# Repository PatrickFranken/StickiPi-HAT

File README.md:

# StickiPi-HAT
RaspberryPI HAT for the Sticki flightlogger

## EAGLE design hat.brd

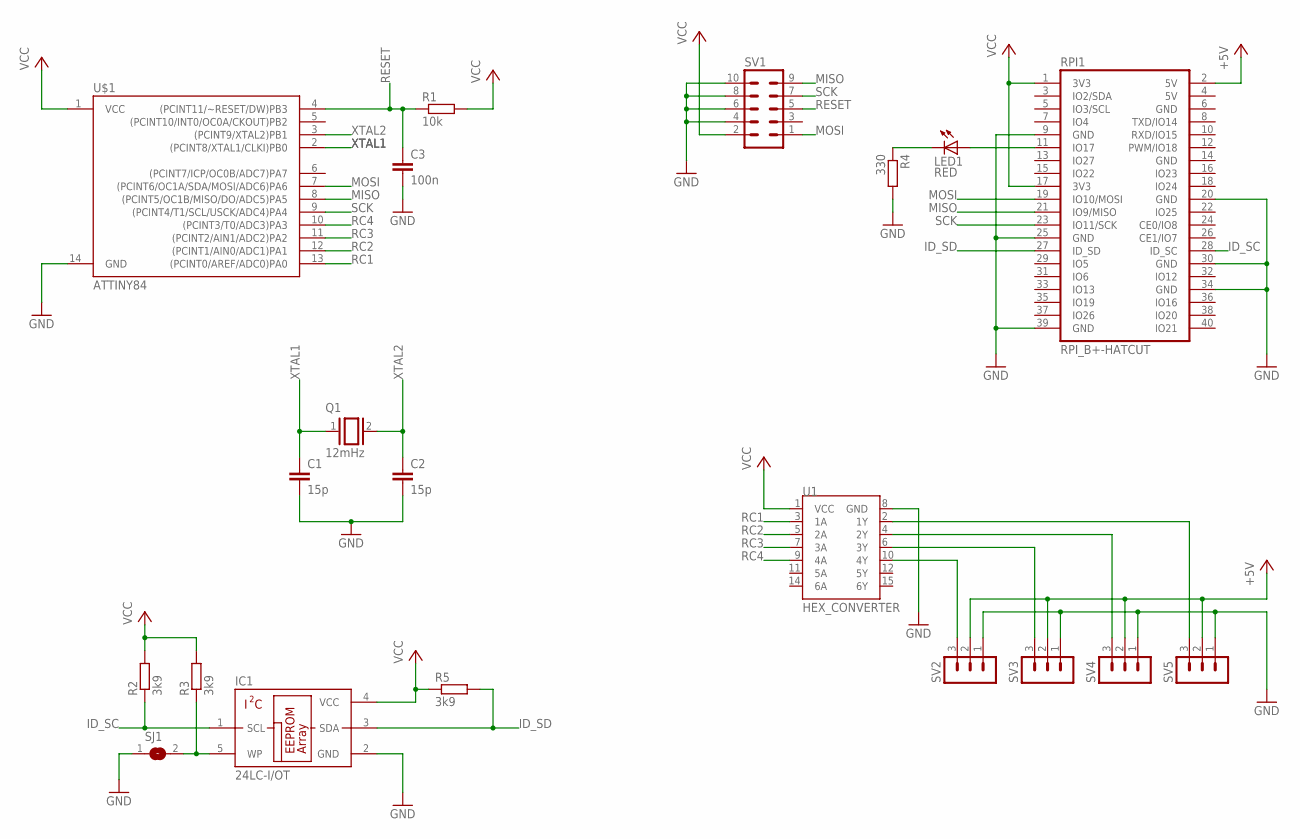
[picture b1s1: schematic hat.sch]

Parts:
C1, C2: 15p; C0603
C3: 100n; C0603
IC1: 24LC-I/OT; SOT23-5
LED1: RED; CHIPLED_0805
Q1: 12mHz; QS
R1: 10k; R0805
R2, R3, R5: 3k9; R0805
R4: 330; R0805
RPI1: RPI_B+-HATCUT; RPI-B+HAT_CUTOUT
SJ1: SJ
SV1: MA05-2
SV2, SV3, SV4, SV5: MA03-1
U1: HEX_CONVERTER; SO016
U$1: ATTINY84; SO14

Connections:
+5V: RPI1.2 (5V), SV2.2, SV3.2, SV4.2, SV5.2
GND: C1.2, C2.2, C3.2, IC1.2 (GND), R4.2, RPI1.9 (GND), RPI1.20 (GND), RPI1.25 (GND), RPI1.30 (GND), RPI1.34 (GND), RPI1.39 (GND), SJ1.1, SV1.4, SV1.6, SV1.8, SV1.10, SV2.1, SV3.1, SV4.1, SV5.1, U1.8 (GND), U$1.14 (GND)
ID_SC: IC1.1 (SCL), R2.1, RPI1.28 (ID_SC)
ID_SD: IC1.3 (SDA), R5.2, RPI1.27 (ID_SD)
MISO: RPI1.21 (IO9/MISO), SV1.9, U$1.8 ((PCINT5/OC1B/MISO/DO/ADC5)PA5)
MOSI: RPI1.19 (IO10/MOSI), SV1.1, U$1.7 ((PCINT6/OC1A/SDA/MOSI/ADC6)PA6)
unnamed: SV2.3, U1.10 (4Y)
unnamed: SV3.3, U1.6 (3Y)
unnamed: SV4.3, U1.4 (2Y)
unnamed: SV5.3, U1.2 (1Y)
unnamed: IC1.5 (WP), R3.1, SJ1.2
unnamed: LED1.A, RPI1.11 (IO17)
unnamed: LED1.C, R4.1
RC1: U1.3 (1A), U$1.13 ((PCINT0/AREF/ADC0)PA0)
RC2: U1.5 (2A), U$1.12 ((PCINT1/AIN0/ADC1)PA1)
RC3: U1.7 (3A), U$1.11 ((PCINT2/AIN1/ADC2)PA2)
RC4: U1.9 (4A), U$1.10 ((PCINT3/T0/ADC3)PA3)
RESET: C3.1, R1.1, SV1.5, U$1.4 ((PCINT11/~RESET/DW)PB3)
SCK: RPI1.23 (IO11/SCK), SV1.7, U$1.9 ((PCINT4/T1/SCL/USCK/ADC4)PA4)
VCC: IC1.4 (VCC), R1.2, R2.2, R3.2, R5.1, RPI1.1 (3V3), RPI1.17 (3V3), SV1.2, U1.1 (VCC), U$1.1 (VCC)
XTAL1: C1.1, Q1.1, U$1.2 ((PCINT8/XTAL1/CLKI)PB0)
XTAL2: C2.1, Q1.2, U$1.3 ((PCINT9/XTAL2)PB1)

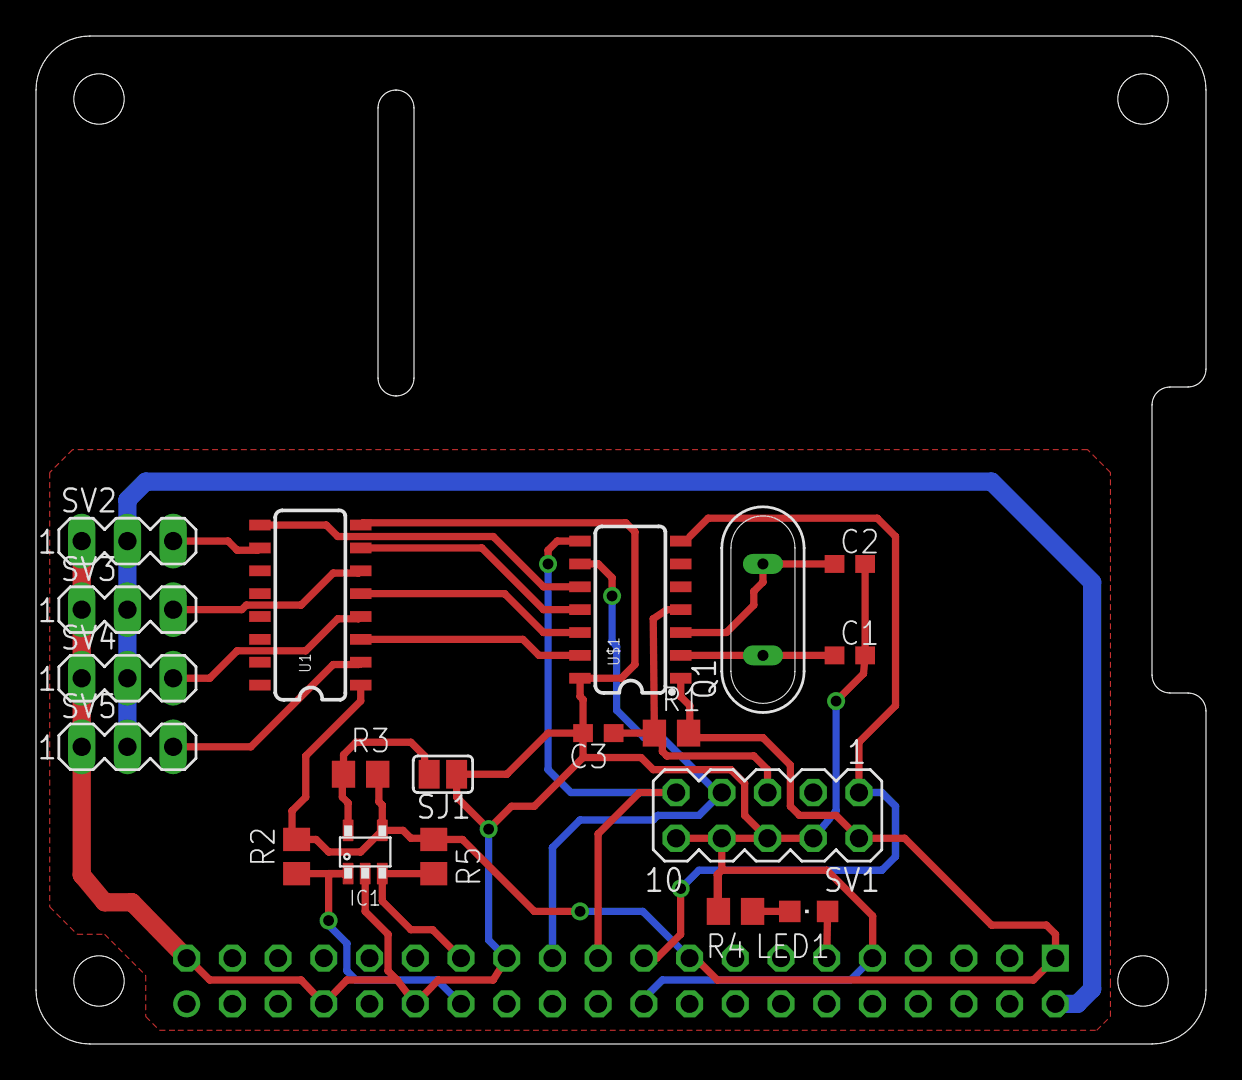
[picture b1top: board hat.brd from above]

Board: 2 copper layers, 65.0 x 56.0 mm, 20 parts (0 on the bottom side), 22 nets.

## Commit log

2016-05-31 Initial commit of schematic
2016-05-31 Work in progess
2016-06-01 Add EAGLE backup files to gitignore
2016-06-04 Add board
2016-06-05 Add proper GND fill plane
2016-06-07 Update gitignore

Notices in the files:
parts and their libraries:
SparkFun-DigitalIC: Licensing: Creative Commons ShareAlike 4.0 International - https://creativecommons.org/licenses/by-sa/4.0
